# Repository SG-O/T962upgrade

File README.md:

**WARNING** This is work in progress! Expect everything to be broken!

# T962upgrade | T-962/T-962A controller upgrade #

## Features ##
### CPU ###
- MAX31850 based K Type thermocouple to single wire converter
- CH340 based USB to UART
- Temperature dependant fan controller

### IO ###
- 4 K Type thermocouple to single wire converter
- 1 UART
- 1 USB
- Push buttons for reset and ISP mode

### Power Supply ###
- Dual linear power supplies for digital and analog circuitry

## Software ##
This was designed for the T-962-improvements Firmware developed by UnifiedEngineering: [https://github.com/UnifiedEngineering/T-962-improvements](https://github.com/UnifiedEngineering/T-962-improvements)

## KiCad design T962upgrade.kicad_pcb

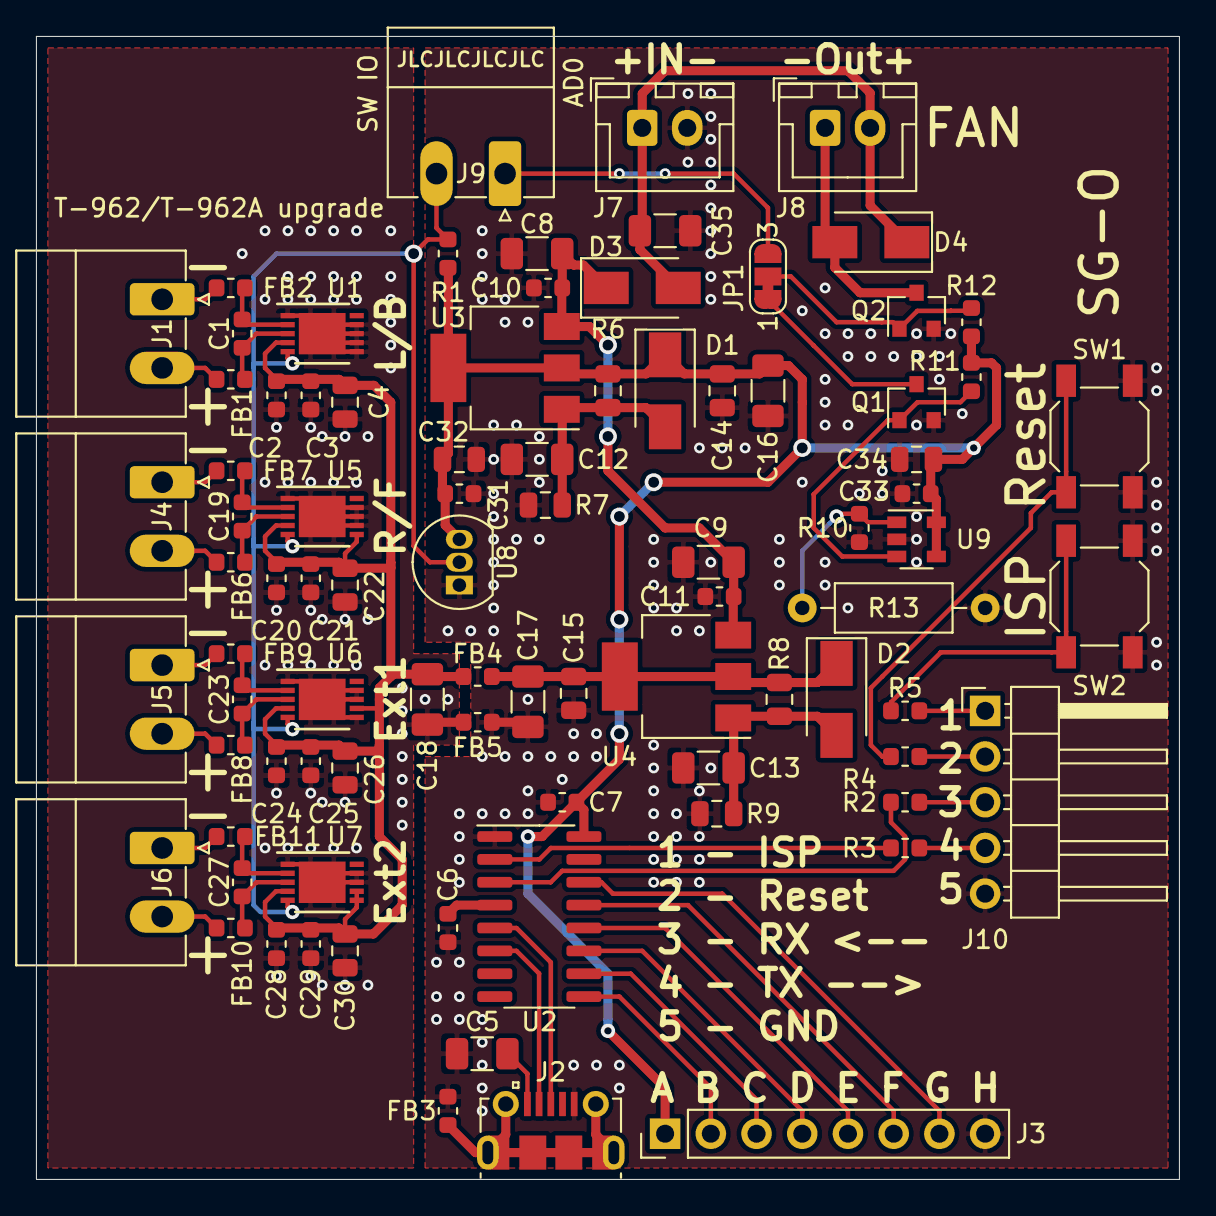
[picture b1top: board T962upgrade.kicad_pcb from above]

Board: 2 copper layers, 63.5 x 63.5 mm, 87 parts (0 on the bottom side), 51 nets.

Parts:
C1, C2, C19, C20, C23, C24, C27, C28: 10n; C_0603_1608Metric
C3, C6, C7, C10, C11, C21, C25, C29, C31, C33: 100n; C_0603_1608Metric
C4, C14, C15, C22, C26, C30, C32, C34: 1u; C_0805_2012Metric
C5, C8, C9, C12, C13, C16, C17, C18, C35: 10u; C_1206_3216Metric
D1, D2, D3, D4: M7; D_SMA
FB1, FB2, FB3, FB4, FB5, FB6, FB7, FB8, FB9, FB10, FB11: Ferrite_Bead_Small; L_0603_1608Metric
J1, J4, J5, J6, J9: K Type; PhoenixContact_MC_1,5_2-G-3.81_1x02_P3.81mm_Horizontal
J2: USB_B_Micro; USB_Micro-B_Molex-105017-0001
J3: USB_X; PinHeader_1x08_P2.54mm_Vertical
J7: Fan In; JST_XH_B2B-XH-A_1x02_P2.50mm_Vertical
J8: Fan Out; JST_XH_B2B-XH-A_1x02_P2.50mm_Vertical
J10: UART; PinHeader_1x05_P2.54mm_Horizontal
JP1: Jumper_Fan; SolderJumper-3_P1.3mm_Bridged12_RoundedPad1.0x1.5mm_NumberL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
Q1, Q2: 2N7002; SOT-23
R1: 4k7; R_0603_1608Metric
R2, R3, R4, R5: 470R; R_0603_1608Metric
R6, R8: 237R; R_0805_2012Metric
R7, R9: 383R; R_0805_2012Metric
R10: 62k; R_0603_1608Metric
R11, R12: 100k; R_0603_1608Metric
R13: DNP; R_Axial_DIN0207_L6.3mm_D2.5mm_P10.16mm_Horizontal
SW1, SW2: Boot; SW_SPST_SKQG_WithStem
U1, U5, U6, U7: MAX31850KATB; TDFN-10-1EP_3x4mm_Pitch0.5mm
U2: CH340C; SOIC-16_3.9x9.9mm_P1.27mm
U3, U4: LM317_3PinPackage; SOT-223-3_TabPin2
U8: DS18S20; TO-92_Inline
U9: TMP709; SOT-23-5

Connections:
+VDC: C8.1, C9.1, C10.1, C11.1, D3.1, U3.3, U4.3
/IO/Fan: J9.1, JP1.3
/ISP: J10.1, R5.2
/RX: J10.3, R2.2
/Reset: J10.2, R4.2
/SW_IO: J9.2, R1.2, U1.5, U5.5, U6.5, U7.5, U8.2
/TX: J10.4, R3.2
/USB/CTS: J3.2, U2.9
/USB/DCD: J3.5, U2.12
/USB/DSR: J3.3, U2.10
/USB/DTR: J3.6, U2.13
/USB/RI: J3.4, U2.11
/USB/RTS: J3.7, U2.14
Earth: FB3.2, J2.6
unnamed: C1.1, FB1.1, U1.3
unnamed: C1.2, FB2.1, U1.2
unnamed: C5.1, J2.1
unnamed: C6.1, U2.4
unnamed: C12.1, D1.2, R6.2, R7.1, U3.1
unnamed: C13.1, D2.2, R8.2, R9.1, U4.1
unnamed: C15.1, C17.1, D2.1, FB4.2, R8.1, U4.2
unnamed: C19.1, FB6.1, U5.3
unnamed: C19.2, FB7.1, U5.2
unnamed: C23.1, FB8.1, U6.3
unnamed: C23.2, FB9.1, U6.2
unnamed: C27.1, FB10.1, U7.3
unnamed: C27.2, FB11.1, U7.2
unnamed: C35.1, D3.2, D4.1, J7.1, J8.2
unnamed: D4.2, J8.1, Q2.3
unnamed: FB1.2, J1.2
unnamed: FB2.2, J1.1
unnamed: FB6.2, J4.2
unnamed: FB7.2, J4.1
unnamed: FB8.2, J5.2
unnamed: FB9.2, J5.1
unnamed: FB10.2, J6.2
unnamed: FB11.2, J6.1
unnamed: J2.2, U2.6
unnamed: J2.3, U2.5
unnamed: JP1.1, Q1.3
unnamed: JP1.2, Q2.1, R12.2
unnamed: Q1.1, R11.2, U9.3
unnamed: R2.1, U2.3
unnamed: R3.1, U2.2
unnamed: R4.1, SW1.1
unnamed: R5.1, SW2.1
unnamed: R10.1, R13.1, U9.1
VDD: C7.1, C14.1, C16.1, C31.1, C32.1, C33.1, C34.1, D1.1, J3.1, R1.1, R6.1, R11.1, R12.1, U2.16, U3.2, U8.3, U9.4, U9.5
VDDA: C2.1, C3.1, C4.1, C18.1, C20.1, C21.1, C22.1, C24.1, C25.1, C26.1, C28.1, C29.1, C30.1, FB4.1, U1.4, U5.4, U5.6, U6.4, U6.7, U7.4, U7.6, U7.7
VSS: C5.2, C6.2, C7.2, C8.2, C9.2, C10.2, C11.2, C12.2, C13.2, C14.2, C15.2, C16.2, C17.2, C31.2, C32.2, C33.2, C34.2, C35.2, FB3.1, FB5.2, J2.5, J3.8, J7.2, J10.5, Q1.2, Q2.2, R7.2, R9.2, R10.2, R13.2, SW1.2, SW2.2, U2.1, U8.1, U9.2
VSSA: C2.2, C3.2, C4.2, C18.2, C20.2, C21.2, C22.2, C24.2, C25.2, C26.2, C28.2, C29.2, C30.2, FB5.1, U1.1, U1.6, U1.7, U1.8, U1.9, U1.11, U5.1, U5.7, U5.8, U5.9, U5.11, U6.1, U6.6, U6.8, U6.9, U6.11, U7.1, U7.8, U7.9, U7.11

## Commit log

2020-02-07 Updated gerber
2020-03-05 Added optional through hole resistor to set fan switch on temperature.
